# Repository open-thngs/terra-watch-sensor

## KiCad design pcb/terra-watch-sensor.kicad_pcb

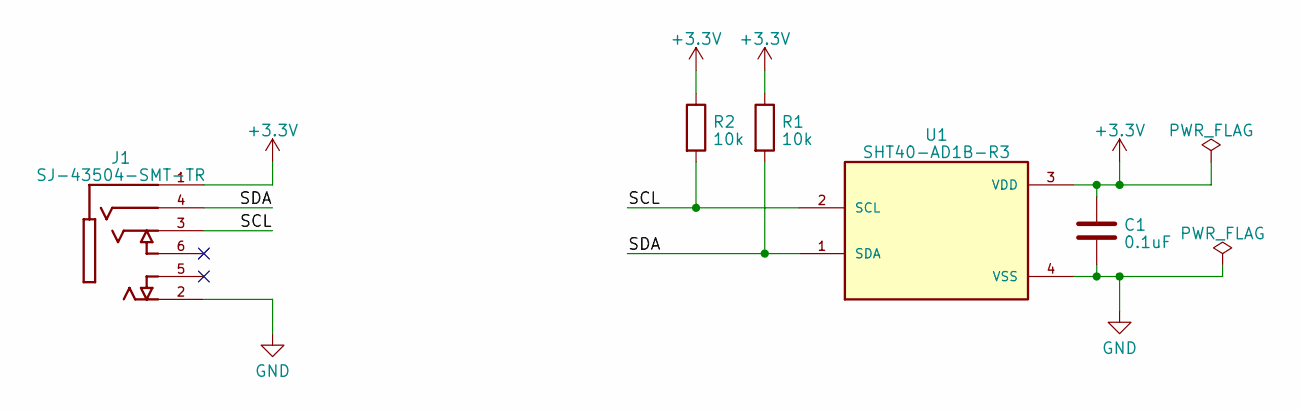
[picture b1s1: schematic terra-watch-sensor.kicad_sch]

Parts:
C1: 0.1uF; C_0603_1608Metric
J1: SJ-43504-SMT-TR; CUI_SJ-43504-SMT-TR; PARTREV 10/08/2019
R1, R2: 10k; R_0603_1608Metric
U1: SHT40-AD1B-R3; SHT4X

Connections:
+3.3V: C1.1, J1.1, R1.1, R2.1, U1.3 (VDD)
/SCL: J1.3, R2.2, U1.2 (SCL)
/SDA: J1.4, R1.2, U1.1 (SDA)
GND: C1.2, J1.2, U1.4 (VSS)

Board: 2 copper layers, 5 parts (0 on the bottom side), 4 nets, no tracks yet.

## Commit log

2023-04-21 Adjust kibot.yml
